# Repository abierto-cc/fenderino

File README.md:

# fenderino

Repositorio para el Fenderino Guitar Shield para Arduino UNO y equivalentes

Diseñado en Suecia con amor para toda la galaxia

# consigue tu kit

Si quieres conseguir el kit para montarlo, visita: https://abierto.cc/shop

# instrucciones de montaje

Puedes ver las instrucciones de montaje paso a paso en: https://sites.google.com/abierto.cc/fenderino

# créditos

Marc Sibila y Jordi Divins de @instroniks y a todos los chicos de su orquesta

Xose Pérez por su contribución con el código MIDI para Arduino UNO y Arduino Leonardo

# autores

D. Cuartielles at abierto.cc (prueba de concepto + código)

J. Garcia at abierto.cc (diseño en KiCAD)

L. Balboa at abierto.cc (gráficos)

# menciones

* Artículo de X. Pérez y explicación sobre el uso de la guitarra con MIDI: http://tinkerman.cat/fenderino-arducaster-the-coolest-guitar/

# licencia para hardware y documentation

<br /><span xmlns:dct="http://purl.org/dc/terms/" href="http://purl.org/dc/dcmitype/Dataset" property="dct:title" rel="dct:type">Fenderino Arducaster</span> by <a xmlns:cc="http://creativecommons.org/ns#" href="https://abierto.cc" property="cc:attributionName" rel="cc:attributionURL">Proyecto Abierto</a> is licensed under a <a rel="license" href="http://creativecommons.org/licenses/by-nc-sa/4.0/">Creative Commons Reconocimiento-NoComercial-CompartirIgual 4.0 Internacional License</a>.<br />Creado a partir de la obra en <a xmlns:dct="http://purl.org/dc/terms/" href="https://github.com/abierto-cc/fenderino" rel="dct:source">https://github.com/abierto-cc/fenderino</a>

# licencia para código de ejemplos

El código está liberado bajo licencia GPLv3, se recomienda leer el fichero de licencia para más información

# abierto

Abierto es una inciativa de D. Cuartielles gracias a la generosa aportación de la Fundación PUIG por intermediación de la Fundación Ashoka de cara a contribuir a la creación de material educativo de libre acceso y circulación

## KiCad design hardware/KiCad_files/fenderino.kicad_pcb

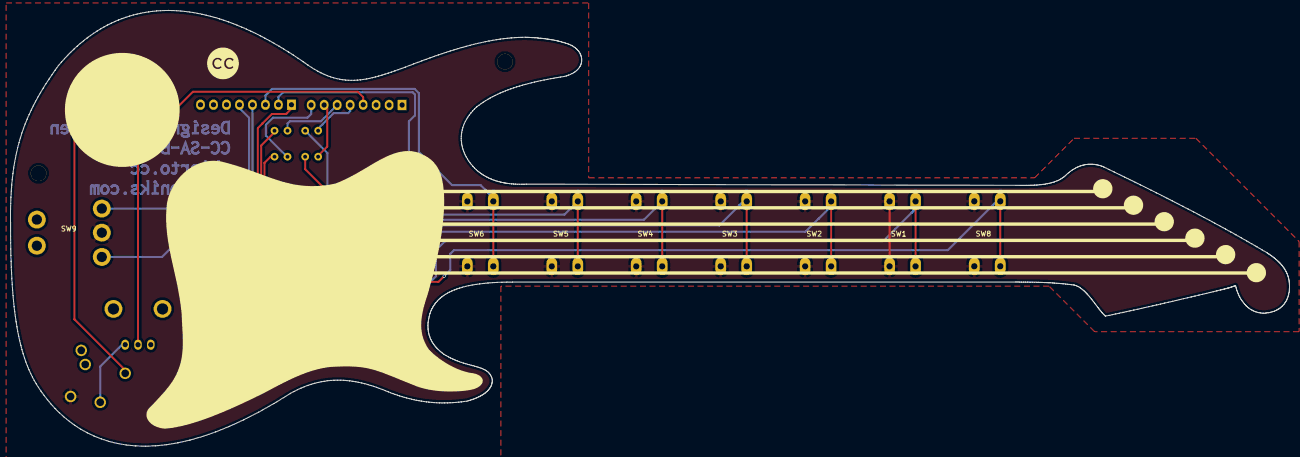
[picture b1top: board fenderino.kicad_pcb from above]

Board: 2 copper layers, 250.1 x 85.2 mm, 21 parts (0 on the bottom side), 24 nets.

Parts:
BZ1: buzzer; buzzer_tmb
D1: LED_Array; Array_4_LED
J1: jack_audio_5pin; jack_huella
P1, P2, P4: CONN_01X08; Pin_Header_Straight_1x08
P3: CONN_01X06; Pin_Header_Straight_1x06
RR1: RR4; r-sil_5
RV1, RV2: POT; trimmer_alps-rk09k1130ah1
SW1, SW2, SW3, SW4, SW5, SW6, SW7, SW8: Switch_DPST; SW_PUSH-12mm
SW9: SWITCH_INV_MSM; switch
svg2mod: G***; svg2mod
svg2mod-rev: G***; svg2mod-rev

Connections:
GND: BZ1.2, J1.1, P2.6, P2.7, RR1.1, RV1.3, SW1.1, SW2.1, SW3.1, SW4.1, SW5.1, SW6.1, SW7.1, SW8.1, SW9.2
unnamed: BZ1.1, J1.4
unnamed: D1.1, RR1.5
unnamed: D1.2, P4.8
unnamed: D1.3, RR1.4
unnamed: D1.4, P4.7
unnamed: D1.5, RR1.3
unnamed: D1.6, P4.6
unnamed: D1.7, RR1.2
unnamed: D1.8, P4.5
unnamed: J1.5, RV2.1
unnamed: P1.1, SW8.2
unnamed: P1.2, SW7.2
unnamed: P1.3, SW6.2
unnamed: P1.4, SW9.3
unnamed: P1.5, SW9.1
unnamed: P3.1, RV1.2
unnamed: P3.2, SW5.2
unnamed: P3.3, SW4.2
unnamed: P3.4, SW3.2
unnamed: P3.5, SW2.2
unnamed: P3.6, SW1.2
unnamed: P4.4, RV2.2
V+: P2.2, RV1.1

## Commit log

2017-05-05 Create LICENCIA
2017-05-05 Update LICENCIA
2017-05-05 Archivos de KiCad y Gerber del Fenderino Guitar Shield
2017-05-05 Added examples and libraries
    Added al of the examples and libraries for the Fenderino Arducaster
2017-05-05 Added Midi Example
2017-07-19 BOM del Fendrino
